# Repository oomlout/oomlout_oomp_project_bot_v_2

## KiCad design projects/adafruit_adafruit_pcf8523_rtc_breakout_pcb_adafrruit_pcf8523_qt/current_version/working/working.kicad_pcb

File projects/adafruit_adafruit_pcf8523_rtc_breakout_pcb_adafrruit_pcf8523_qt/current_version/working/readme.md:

# adafruit_pcf8523_rtc_breakout_pcb
 
## summary 
* id: adafruit_adafruit_pcf8523_rtc_breakout_pcb_adafrruit_pcf8523_qt
* user: adafruit
* name: adafruit_pcf8523_rtc_breakout_pcb
* board: adafrruit_pcf8523_qt
* repo: https://github.com/adafruit/Adafruit-PCF8523-RTC-Breakout-PCB

* src_file_repo_sch: 
* src_file_repo_sch_link: https://github.com/adafruit/Adafruit-PCF8523-RTC-Breakout-PCB/tree/master/
* full details link: https://github.com/oomlout/oomlout_oomp_project_bot_v_2/tree/main/projects/adafruit_adafruit_pcf8523_rtc_breakout_pcb_adafrruit_pcf8523_qt/current_version/working  

## schematic  
  
[schematic (pdf)](working_schematic.pdf) 

## pcb  

[board (pdf)](working.pdf)  

## working_bom
| Id | Designator | Footprint | Quantity | Designation | Supplier and ref |  | None | 
| --- | --- | --- | --- | --- | --- | --- | --- | 
| 1 | CONN3,CONN4 | JST_SH4 | 2 | STEMMA_I2C_QT |  |  | [''] | 
| 2 | D1 | CHIPLED_0603_NOOUTLINE | 1 | GREEN |  |  | [''] | 
| 3 | U$22 | ADAFRUIT_3.5MM | 1 |  |  |  | [''] | 
| 4 | R3 | 0603-NO | 1 | 1K |  |  | [''] | 
| 5 | IC1 | SOIC8_150MIL | 1 | RTC_PCF8523T |  |  | [''] | 
| 6 | R1 | RESPACK_4X0603 | 1 | 10K |  |  | [''] | 
| 7 | U$19,U$21,U$17,U$9 | MOUNTINGHOLE_3.0_PLATEDTHIN | 4 | MOUNTINGHOLE3.0THIN |  |  | [''] | 
| 8 | C4,C3,C1 | 0805-NO | 3 | 10uF |  |  | [''] | 
| 9 | SJ1 | SOLDERJUMPER_CLOSEDWIRE | 1 |  |  |  | [''] | 
| 10 | JP2 | 1X05_ROUND_70 | 1 |  |  |  | [''] | 
| 11 | FID3,FID4,FID1,FID2 | FIDUCIAL_1MM | 4 | FIDUCIAL_1MM |  |  | [''] | 
| 12 | C5 | 0603-NO | 1 | 0.1uF |  |  | [''] | 
| 13 | Q1 | XTAL3215 | 1 | 32.768 |  |  | [''] | 
| 14 | U$25 | PCBFEAT-REV-040 | 1 |  |  |  | [''] | 
| 15 | U$31 | STEMMAQT | 1 |  |  |  | [''] | 
| 16 | B1 | CR1220 | 1 | CR1220 |  |  | [''] | 

## bom_schematic
| Ref | Qnty | Value | Cmp name | Footprint | Description | Vendor | DNP | 
| --- | --- | --- | --- | --- | --- | --- | --- | 
| B1 | 1 | CR1220 | BATTERYCR1220_SMT | working:CR1220 |  |  |  | 
| C1, C3, C4 | 3 | 10uF | CAP_CERAMIC0805-NOOUTLINE | working:0805-NO |  |  |  | 
| C5 | 1 | 0.1uF | CAP_CERAMIC0603_NO | working:0603-NO |  |  |  | 
| CONN3, CONN4 | 2 | STEMMA_I2C_QT | STEMMA_I2C_QT | working:JST_SH4 |  |  |  | 
| D1 | 1 | GREEN | LED0603_NOOUTLINE | working:CHIPLED_0603_NOOUTLINE |  |  |  | 
| FID1, FID2, FID3, FID4 | 4 | FIDUCIAL_1MM | FIDUCIAL_1MM | working:FIDUCIAL_1MM |  |  |  | 
| IC1 | 1 | RTC_PCF8523T | RTC_PCF8523T | working:SOIC8_150MIL |  |  |  | 
| JP2 | 1 | HEADER-1X570MIL | HEADER-1X570MIL | working:1X05_ROUND_70 |  |  |  | 
| Q1 | 1 | 32.768 | CRYSTAL_3215 | working:XTAL3215 |  |  |  | 
| R1 | 1 | 10K | RESISTOR_4PACK | working:RESPACK_4X0603 |  |  |  | 
| R3 | 1 | 1K | RESISTOR_0603_NOOUT | working:0603-NO |  |  |  | 
| SJ1 | 1 | SOLDERJUMPER_CLOSED | SOLDERJUMPER_CLOSED | working:SOLDERJUMPER_CLOSEDWIRE |  |  |  | 
| U$9, U$17, U$19, U$21 | 4 | MOUNTINGHOLE3.0THIN | MOUNTINGHOLE3.0THIN | working:MOUNTINGHOLE_3.0_PLATEDTHIN |  |  |  | 

## mounting_holes
| x | y | package | value | ref | size | 
| --- | --- | --- | --- | --- | --- | 
| 0.0 | 12.7 | MOUNTINGHOLE_3.0_PLATEDTHIN | MOUNTINGHOLE3.0THIN | U$9 | m3 | 
| 20.32 | 12.7 | MOUNTINGHOLE_3.0_PLATEDTHIN | MOUNTINGHOLE3.0THIN | U$17 | m3 | 
| 0.0 | 0.0 | MOUNTINGHOLE_3.0_PLATEDTHIN | MOUNTINGHOLE3.0THIN | U$19 | m3 | 
| 20.32 | 0.0 | MOUNTINGHOLE_3.0_PLATEDTHIN | MOUNTINGHOLE3.0THIN | U$21 | m3 |

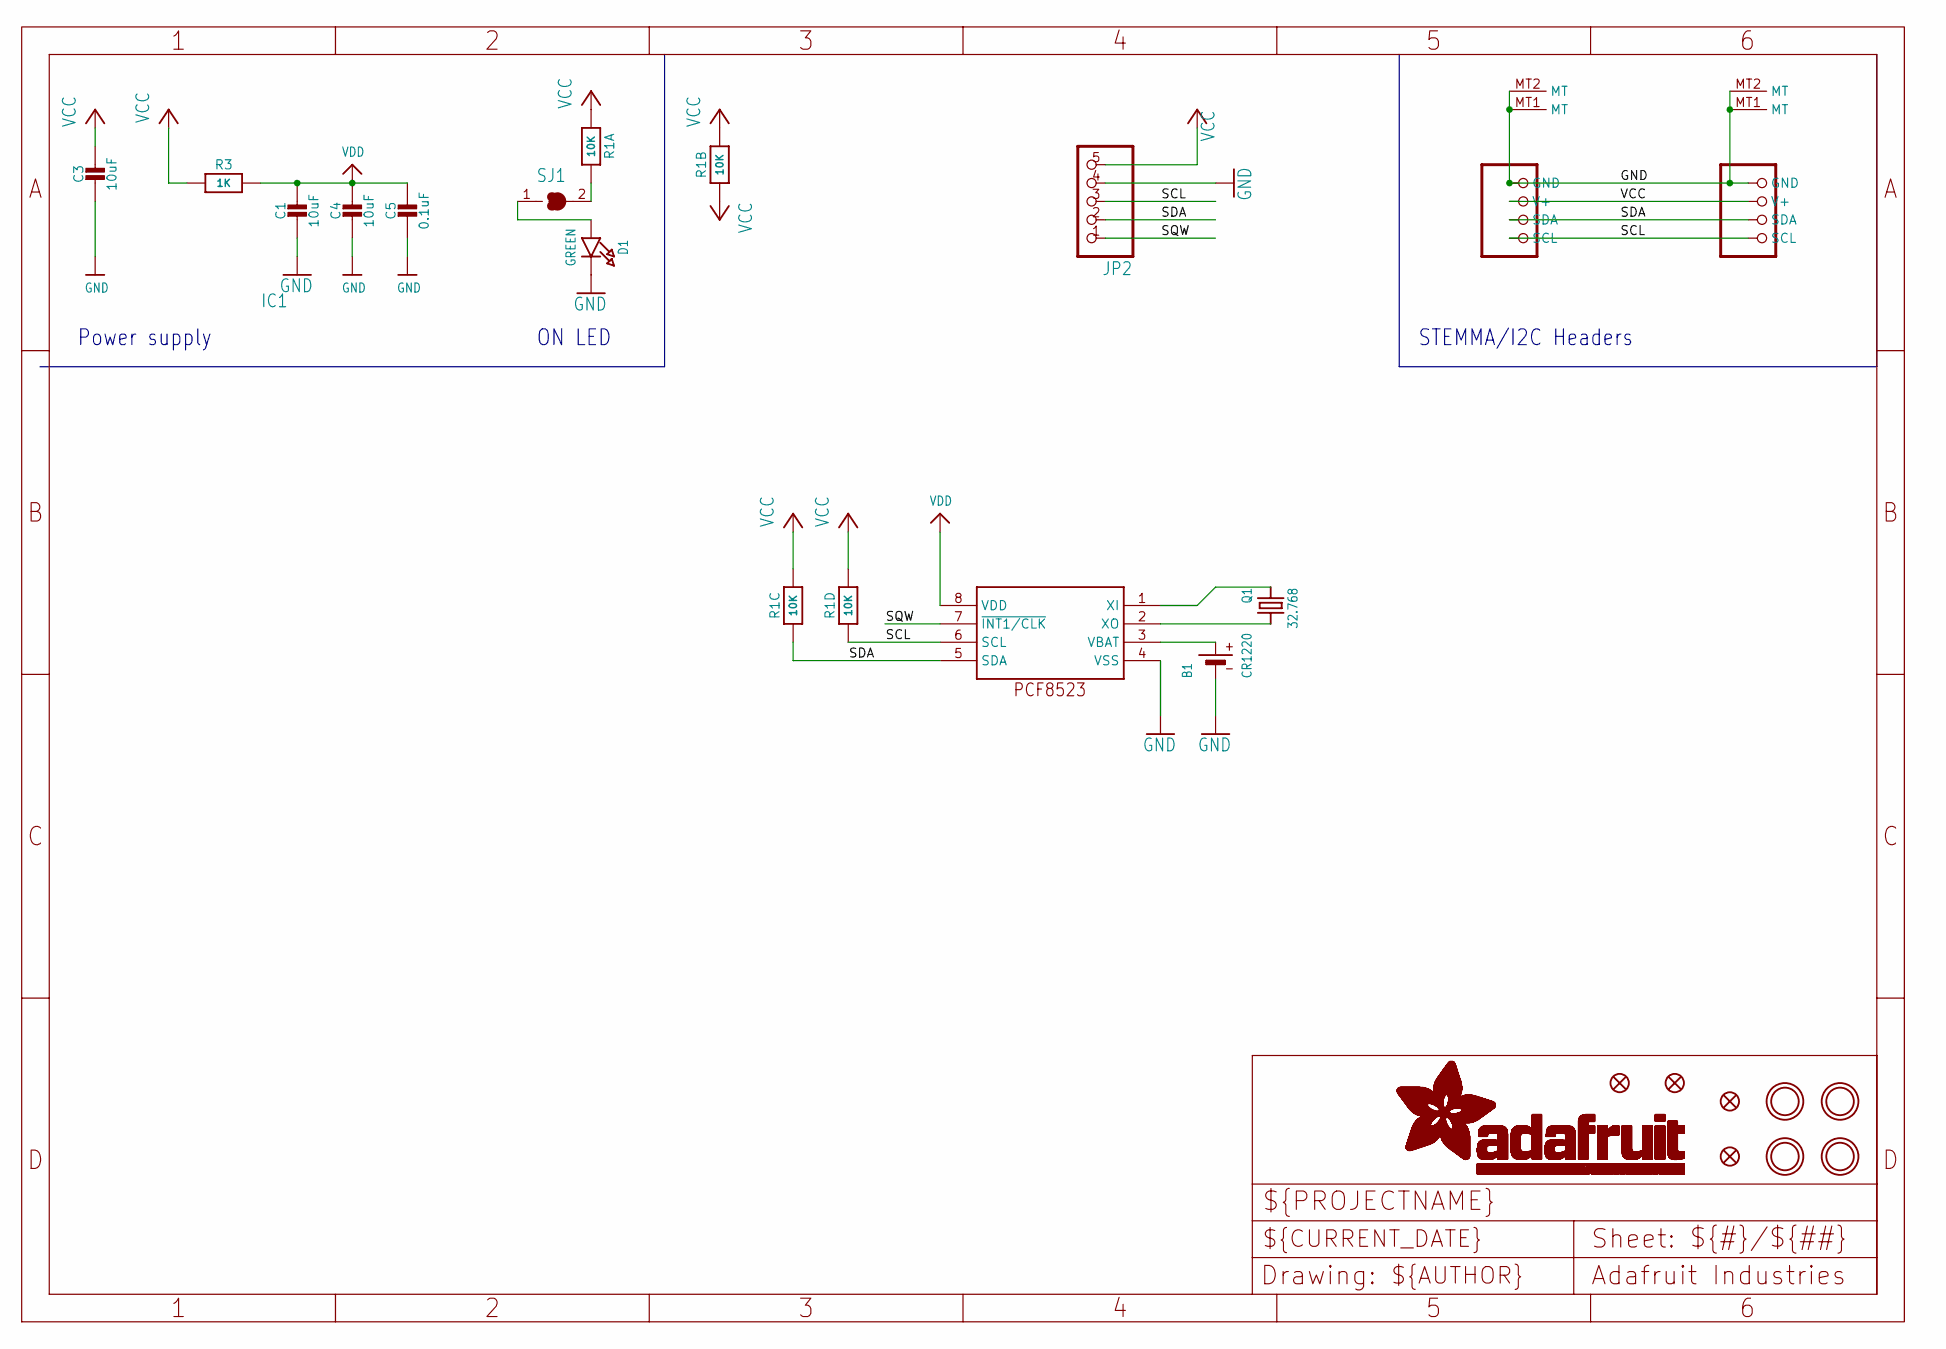
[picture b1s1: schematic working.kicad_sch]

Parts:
B1: CR1220
C1, C3, C4: 10uF; 0805-NO
C5: 0.1uF; 0603-NO
CONN3, CONN4: STEMMA_I2C_QT; JST_SH4
D1: GREEN; CHIPLED_0603_NOOUTLINE
FID1, FID2, FID3, FID4: FIDUCIAL_1MM
IC1: RTC_PCF8523T; SOIC8_150MIL
JP2: HEADER-1X570MIL; 1X05_ROUND_70
Q1: 32.768; XTAL3215
R1: 10K; RESPACK_4X0603
R3: 1K; 0603-NO
SJ1: SOLDERJUMPER_CLOSED; SOLDERJUMPER_CLOSEDWIRE
U$9, U$17, U$19, U$21: MOUNTINGHOLE3.0THIN; MOUNTINGHOLE_3.0_PLATEDTHIN

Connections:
GND: B1.-, C1.2, C3.2, C4.2, C5.2, CONN3.1 (GND), CONN3.MT1 (MT), CONN3.MT2 (MT), CONN4.1 (GND), CONN4.MT1 (MT), CONN4.MT2 (MT), D1.C, IC1.4 (VSS), JP2.4
unnamed: R1.8 (2), SJ1.2
unnamed: D1.A, SJ1.1
unnamed: IC1.1 (XI), Q1.P$1 (1)
unnamed: IC1.2 (XO), Q1.P$2 (2)
SCL: CONN3.4 (SCL), CONN4.4 (SCL), IC1.6 (SCL), JP2.3, R1.4 (1)
SDA: CONN3.3 (SDA), CONN4.3 (SDA), IC1.5 (SDA), JP2.2, R1.3 (1)
SQW: IC1.7 (~INT1/CLK), JP2.1
VBAT: B1.+$1 (+), B1.+$2 (+), IC1.3 (VBAT)
VCC: C3.1, CONN3.2 (V+), CONN4.2 (V+), JP2.5, R1.1, R1.2 (1), R1.5 (2), R1.6 (2), R1.7 (2), R3.1
VDD: C1.1, C4.1, C5.1, IC1.8 (VDD), R3.2

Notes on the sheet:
STEMMA/I2C Headers
Power supply
ON LED

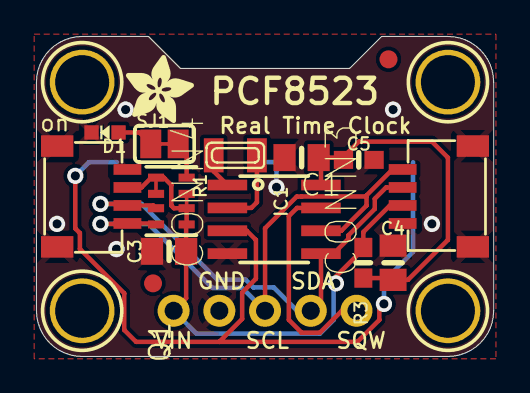
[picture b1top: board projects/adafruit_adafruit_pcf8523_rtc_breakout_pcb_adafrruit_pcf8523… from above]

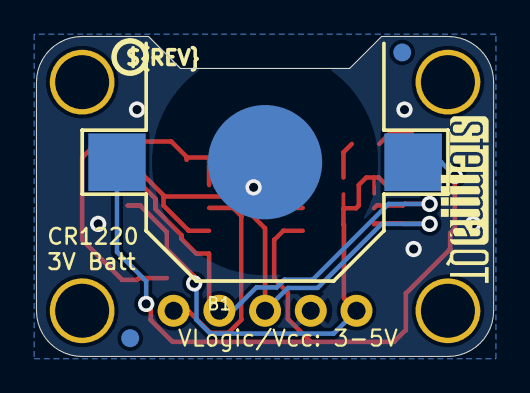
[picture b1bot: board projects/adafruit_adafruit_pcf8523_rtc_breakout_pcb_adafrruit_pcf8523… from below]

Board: 16 copper layers, 25.4 x 17.8 mm, 25 parts (5 on the bottom side), 11 nets.

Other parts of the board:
U$22: ADAFRUIT_3.5MM
U$25: PCBFEAT-REV-040
U$31: STEMMAQT

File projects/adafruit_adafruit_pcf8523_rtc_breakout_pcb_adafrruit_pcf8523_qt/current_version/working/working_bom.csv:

"Id";"Designator";"Footprint";"Quantity";"Designation";"Supplier and ref";
1;"CONN3,CONN4";"JST_SH4";2;"STEMMA_I2C_QT";;;
2;"D1";"CHIPLED_0603_NOOUTLINE";1;"GREEN";;;
3;"U$22";"ADAFRUIT_3.5MM";1;"";;;
4;"R3";"0603-NO";1;"1K";;;
5;"IC1";"SOIC8_150MIL";1;"RTC_PCF8523T";;;
6;"R1";"RESPACK_4X0603";1;"10K";;;
7;"U$19,U$21,U$17,U$9";"MOUNTINGHOLE_3.0_PLATEDTHIN";4;"MOUNTINGHOLE3.0THIN";;;
8;"C4,C3,C1";"0805-NO";3;"10uF";;;
9;"SJ1";"SOLDERJUMPER_CLOSEDWIRE";1;"";;;
10;"JP2";"1X05_ROUND_70";1;"";;;
11;"FID3,FID4,FID1,FID2";"FIDUCIAL_1MM";4;"FIDUCIAL_1MM";;;
12;"C5";"0603-NO";1;"0.1uF";;;
13;"Q1";"XTAL3215";1;"32.768";;;
14;"U$25";"PCBFEAT-REV-040";1;"";;;
15;"U$31";"STEMMAQT";1;"";;;
16;"B1";"CR1220";1;"CR1220";;;

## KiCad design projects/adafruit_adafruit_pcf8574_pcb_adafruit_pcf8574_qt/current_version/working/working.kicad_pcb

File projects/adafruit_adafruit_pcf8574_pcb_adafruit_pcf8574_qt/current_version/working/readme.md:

# adafruit_pcf8574_pcb
 
## summary 
* id: adafruit_adafruit_pcf8574_pcb_adafruit_pcf8574_qt
* user: adafruit
* name: adafruit_pcf8574_pcb
* board: adafruit_pcf8574_qt
* repo: https://github.com/adafruit/Adafruit-PCF8574-PCB

* src_file_repo_sch: 
* src_file_repo_sch_link: https://github.com/adafruit/Adafruit-PCF8574-PCB/tree/main/
* full details link: https://github.com/oomlout/oomlout_oomp_project_bot_v_2/tree/main/projects/adafruit_adafruit_pcf8574_pcb_adafruit_pcf8574_qt/current_version/working  

## schematic  
  
[schematic (pdf)](working_schematic.pdf) 

## pcb  

[board (pdf)](working.pdf)  

## working_bom
| Id | Designator | Footprint | Quantity | Designation | Supplier and ref |  | None | 
| --- | --- | --- | --- | --- | --- | --- | --- | 
| 1 | U$19,U$21 | MOUNTINGHOLE_2.5_PLATED | 2 | MOUNTINGHOLE2.5 |  |  | [''] | 
| 2 | IC1 | VQFN20_3.5X4.5 | 1 | PCF8574RGY |  |  | [''] | 
| 3 | FID4,FID3 | FIDUCIAL_1MM | 2 | FIDUCIAL_1MM |  |  | [''] | 
| 4 | R3,R1 | RESPACK_4X0603 | 2 | 10K |  |  | [''] | 
| 5 | CONN4,CONN3 | JST_SH4 | 2 | STEMMA_I2C_QT |  |  | [''] | 
| 6 | D1 | CHIPLED_0603_NOOUTLINE | 1 | GREEN |  |  | [''] | 
| 7 | U$11 | SYMBOL_PLUS | 1 |  |  |  | [''] | 
| 8 | C1 | 0603-NO | 1 | 0.1uF |  |  | [''] | 
| 9 | U$9 | SYMBOL_MINUS | 1 |  |  |  | [''] | 
| 10 | JP1 | 1X06_ROUND_70 | 1 |  |  |  | [''] | 
| 11 | C3 | 0805-NO | 1 | 10uF |  |  | [''] | 
| 12 | JP3 | 1X10_ROUND70 | 1 |  |  |  | [''] | 
| 13 | U$8 | ADAFRUIT_2.5MM | 1 |  |  |  | [''] | 
| 14 | SJ4 | SOLDERJUMPER_CLOSEDWIRE | 1 |  |  |  | [''] | 
| 15 | SJ1,SJ2,SJ3 | SOLDERJUMPER_ARROW_NOPASTE | 3 |  |  |  | [''] | 
| 16 | U$25 | PCBFEAT-REV-040 | 1 |  |  |  | [''] | 
| 17 | U$30,U$31 | STEMMAQT | 2 |  |  |  | [''] | 

## bom_schematic
| Ref | Qnty | Value | Cmp name | Footprint | Description | Vendor | DNP | 
| --- | --- | --- | --- | --- | --- | --- | --- | 
| C1 | 1 | 0.1uF | CAP_CERAMIC0603_NO | working:0603-NO |  |  |  | 
| C3 | 1 | 10uF | CAP_CERAMIC0805-NOOUTLINE | working:0805-NO |  |  |  | 
| CONN3, CONN4 | 2 | STEMMA_I2C_QT | STEMMA_I2C_QT | working:JST_SH4 |  |  |  | 
| D1 | 1 | GREEN | LED0603_NOOUTLINE | working:CHIPLED_0603_NOOUTLINE |  |  |  | 
| FID3, FID4 | 2 | FIDUCIAL_1MM | FIDUCIAL_1MM | working:FIDUCIAL_1MM |  |  |  | 
| IC1 | 1 | PCF8574RGY | PCF8574RGY | working:VQFN20_3.5X4.5 |  |  |  | 
| JP1 | 1 | HEADER-1X670MIL | HEADER-1X670MIL | working:1X06_ROUND_70 |  |  |  | 
| JP3 | 1 | HEADER-1X1070MIL | HEADER-1X1070MIL | working:1X10_ROUND70 |  |  |  | 
| R1, R3 | 2 | 10K | RESISTOR_4PACK | working:RESPACK_4X0603 |  |  |  | 
| SJ1, SJ2, SJ3 | 3 | SOLDERJUMPER | SOLDERJUMPER | working:SOLDERJUMPER_ARROW_NOPASTE |  |  |  | 
| SJ4 | 1 | SOLDERJUMPERCLOSED | SOLDERJUMPERCLOSED | working:SOLDERJUMPER_CLOSEDWIRE |  |  |  | 
| U$19, U$21 | 2 | MOUNTINGHOLE2.5 | MOUNTINGHOLE2.5 | working:MOUNTINGHOLE_2.5_PLATED |  |  |  | 

## mounting_holes
| x | y | package | value | ref | size | 
| --- | --- | --- | --- | --- | --- | 
| 0.0 | 0.0 | MOUNTINGHOLE_2.5_PLATED | MOUNTINGHOLE2.5 | U$19 | m3 | 
| 20.32 | 0.0 | MOUNTINGHOLE_2.5_PLATED | MOUNTINGHOLE2.5 | U$21 | m3 |

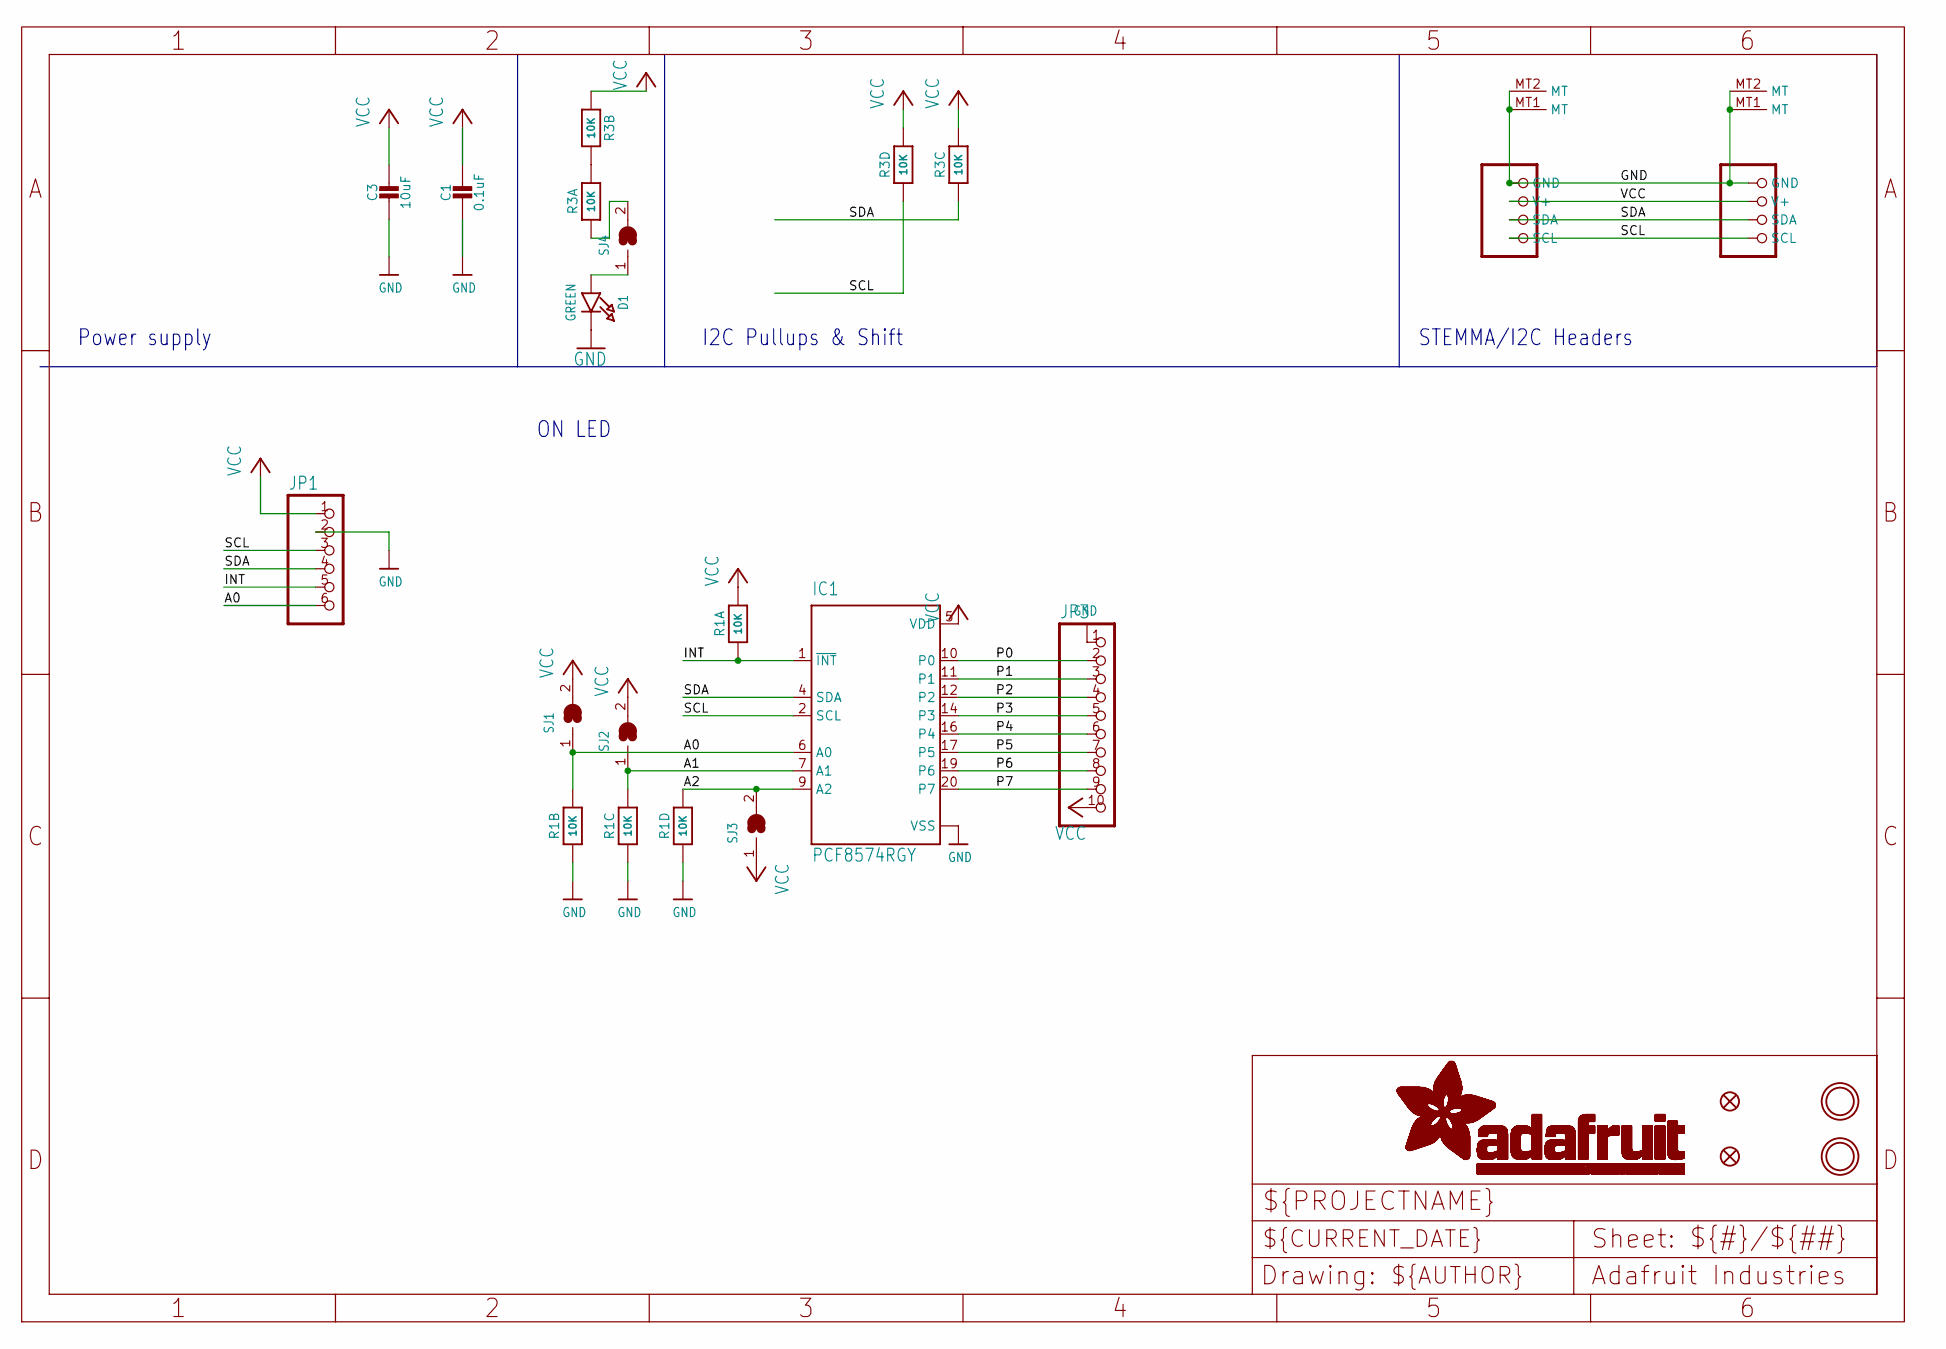
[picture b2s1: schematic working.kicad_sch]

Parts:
C1: 0.1uF; 0603-NO
C3: 10uF; 0805-NO
CONN3, CONN4: STEMMA_I2C_QT; JST_SH4
D1: GREEN; CHIPLED_0603_NOOUTLINE
FID3, FID4: FIDUCIAL_1MM
IC1: PCF8574RGY; VQFN20_3.5X4.5
JP1: HEADER-1X670MIL; 1X06_ROUND_70
JP3: HEADER-1X1070MIL; 1X10_ROUND70
R1, R3: 10K; RESPACK_4X0603
SJ1, SJ2, SJ3: SOLDERJUMPER; SOLDERJUMPER_ARROW_NOPASTE
SJ4: SOLDERJUMPERCLOSED; SOLDERJUMPER_CLOSEDWIRE
U$19, U$21: MOUNTINGHOLE2.5; MOUNTINGHOLE_2.5_PLATED

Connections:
A0: IC1.6 (A0), JP1.6, R1.7 (2), SJ1.1
A1: IC1.7 (A1), R1.6 (2), SJ2.1
A2: IC1.9 (A2), R1.5 (2), SJ3.2
GND: C1.2, C3.2, CONN3.1 (GND), CONN3.MT1 (MT), CONN3.MT2 (MT), CONN4.1 (GND), CONN4.MT1 (MT), CONN4.MT2 (MT), D1.C, IC1.15 (VSS), IC1.21 (VSS), JP1.2, JP3.1, R1.2 (1), R1.3 (1), R1.4 (1)
INT: IC1.1 (~INT), JP1.5, R1.1
unnamed: R3.1, SJ4.2
unnamed: R3.7 (2), R3.8 (2)
unnamed: D1.A, SJ4.1
P0: IC1.10 (P0), JP3.2
P1: IC1.11 (P1), JP3.3
P2: IC1.12 (P2), JP3.4
P3: IC1.14 (P3), JP3.5
P4: IC1.16 (P4), JP3.6
P5: IC1.17 (P5), JP3.7
P6: IC1.19 (P6), JP3.8
P7: IC1.20 (P7), JP3.9
SCL: CONN3.4 (SCL), CONN4.4 (SCL), IC1.2 (SCL), JP1.3, R3.4 (1)
SDA: CONN3.3 (SDA), CONN4.3 (SDA), IC1.4 (SDA), JP1.4, R3.3 (1)
VCC: C1.1, C3.1, CONN3.2 (V+), CONN4.2 (V+), IC1.5 (VDD), JP1.1, JP3.10, R1.8 (2), R3.2 (1), R3.5 (2), R3.6 (2), SJ1.2, SJ2.2, SJ3.1

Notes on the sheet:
STEMMA/I2C Headers
Power supply
I2C Pullups & Shift
ON LED

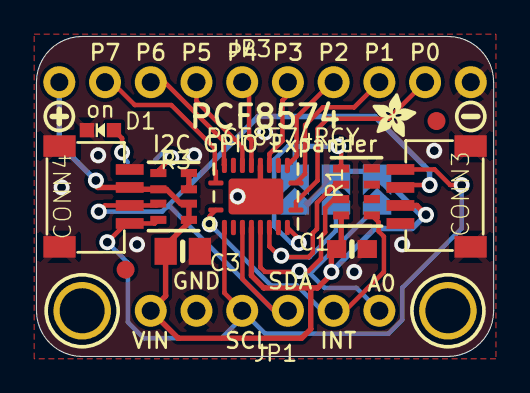
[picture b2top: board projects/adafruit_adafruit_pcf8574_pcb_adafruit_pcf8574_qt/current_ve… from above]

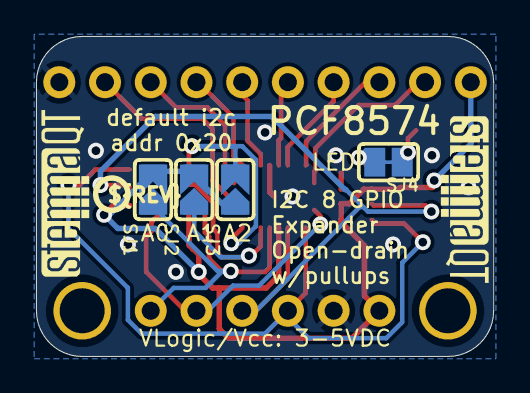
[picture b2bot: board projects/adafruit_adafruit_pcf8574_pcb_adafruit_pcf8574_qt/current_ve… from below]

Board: 2 copper layers, 25.4 x 17.8 mm, 24 parts (7 on the bottom side), 19 nets.

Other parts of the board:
U$8: ADAFRUIT_2.5MM
U$9: SYMBOL_MINUS
U$11: SYMBOL_PLUS
U$25: PCBFEAT-REV-040
U$30, U$31: STEMMAQT

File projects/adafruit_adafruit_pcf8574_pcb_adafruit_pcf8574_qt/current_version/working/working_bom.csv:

"Id";"Designator";"Footprint";"Quantity";"Designation";"Supplier and ref";
1;"U$19,U$21";"MOUNTINGHOLE_2.5_PLATED";2;"MOUNTINGHOLE2.5";;;
2;"IC1";"VQFN20_3.5X4.5";1;"PCF8574RGY";;;
3;"FID4,FID3";"FIDUCIAL_1MM";2;"FIDUCIAL_1MM";;;
4;"R3,R1";"RESPACK_4X0603";2;"10K";;;
5;"CONN4,CONN3";"JST_SH4";2;"STEMMA_I2C_QT";;;
6;"D1";"CHIPLED_0603_NOOUTLINE";1;"GREEN";;;
7;"U$11";"SYMBOL_PLUS";1;"";;;
8;"C1";"0603-NO";1;"0.1uF";;;
9;"U$9";"SYMBOL_MINUS";1;"";;;
10;"JP1";"1X06_ROUND_70";1;"";;;
11;"C3";"0805-NO";1;"10uF";;;
12;"JP3";"1X10_ROUND70";1;"";;;
13;"U$8";"ADAFRUIT_2.5MM";1;"";;;
14;"SJ4";"SOLDERJUMPER_CLOSEDWIRE";1;"";;;
15;"SJ1,SJ2,SJ3";"SOLDERJUMPER_ARROW_NOPASTE";3;"";;;
16;"U$25";"PCBFEAT-REV-040";1;"";;;
17;"U$30,U$31";"STEMMAQT";2;"";;;

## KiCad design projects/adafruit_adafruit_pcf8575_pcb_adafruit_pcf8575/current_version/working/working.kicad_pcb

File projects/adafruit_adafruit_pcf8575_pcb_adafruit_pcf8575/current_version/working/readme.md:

# adafruit_pcf8575_pcb
 
## summary 
* id: adafruit_adafruit_pcf8575_pcb_adafruit_pcf8575
* user: adafruit
* name: adafruit_pcf8575_pcb
* board: adafruit_pcf8575
* repo: https://github.com/adafruit/Adafruit-PCF8575-PCB

* src_file_repo_sch: 
* src_file_repo_sch_link: https://github.com/adafruit/Adafruit-PCF8575-PCB/tree/main/
* full details link: https://github.com/oomlout/oomlout_oomp_project_bot_v_2/tree/main/projects/adafruit_adafruit_pcf8575_pcb_adafruit_pcf8575/current_version/working  

## schematic  
  
[schematic (pdf)](working_schematic.pdf) 

## pcb  

[board (pdf)](working.pdf)  

## working_bom
| Id | Designator | Footprint | Quantity | Designation | Supplier and ref |  | None | 
| --- | --- | --- | --- | --- | --- | --- | --- | 
| 1 | U$17,U$1,U$21,U$19 | MOUNTINGHOLE_2.5_PLATED | 4 | MOUNTINGHOLE2.5 |  |  | [''] | 
| 2 | IC2 | QFN24_4MM_SMSC | 1 | PCF8575 |  |  | [''] | 
| 3 | U$22 | ADAFRUIT_3.5MM | 1 |  |  |  | [''] | 
| 4 | CONN3,CONN4 | JST_SH4 | 2 | STEMMA_I2C_QT |  |  | [''] | 
| 5 | JP6,JP2,JP7,JP8 | 1X08_ROUND_70 | 4 |  |  |  | [''] | 
| 6 | D1 | CHIPLED_0603_NOOUTLINE | 1 | GREEN |  |  | [''] | 
| 7 | FID3,FID4 | FIDUCIAL_1MM | 2 | FIDUCIAL_1MM |  |  | [''] | 
| 8 | R1,R3 | RESPACK_4X0603 | 2 | 10K Pack |  |  | [''] | 
| 9 | U$3 | SYMBOL_MINUS | 1 |  |  |  | [''] | 
| 10 | C1 | 0603-NO | 1 | 0.1uF |  |  | [''] | 
| 11 | C3,C2 | 0805-NO | 2 | 10uF |  |  | [''] | 
| 12 | JP4,JP3 | 1X04_ROUND | 2 |  |  |  | [''] | 
| 13 | U$2 | SYMBOL_PLUS | 1 |  |  |  | [''] | 
| 14 | ADDR2,ADDR1,ADDR0 | SOLDERJUMPER_ARROW_NOPASTE | 3 |  |  |  | [''] | 
| 15 | U$30,U$31 | STEMMAQT | 2 |  |  |  | [''] | 
| 16 | SJ1 | SOLDERJUMPER_CLOSEDWIRE | 1 |  |  |  | [''] | 
| 17 | U$25 | PCBFEAT-REV-040 | 1 |  |  |  | [''] | 

## bom_schematic
| Ref | Qnty | Value | Cmp name | Footprint | Description | Vendor | DNP | 
| --- | --- | --- | --- | --- | --- | --- | --- | 
| ADDR0, ADDR1, ADDR2 | 3 | SOLDERJUMPER | SOLDERJUMPER | working:SOLDERJUMPER_ARROW_NOPASTE |  |  |  | 
| C1 | 1 | 0.1uF | CAP_CERAMIC0603_NO | working:0603-NO |  |  |  | 
| C2, C3 | 2 | 10uF | CAP_CERAMIC0805-NOOUTLINE | working:0805-NO |  |  |  | 
| CONN3, CONN4 | 2 | STEMMA_I2C_QT | STEMMA_I2C_QT | working:JST_SH4 |  |  |  | 
| D1 | 1 | GREEN | LED0603_NOOUTLINE | working:CHIPLED_0603_NOOUTLINE |  |  |  | 
| FID3, FID4 | 2 | FIDUCIAL_1MM | FIDUCIAL_1MM | working:FIDUCIAL_1MM |  |  |  | 
| IC2 | 1 | PCF8575 | PCF8575 | working:QFN24_4MM_SMSC |  |  |  | 
| JP2, JP6, JP7, JP8 | 4 | HEADER-1X870MIL | HEADER-1X870MIL | working:1X08_ROUND_70 |  |  |  | 
| JP3, JP4 | 2 | HEADER-1X4ROUND | HEADER-1X4ROUND | working:1X04_ROUND |  |  |  | 
| R1, R3 | 2 | 10K Pack | RESISTOR_4PACK | working:RESPACK_4X0603 |  |  |  | 
| SJ1 | 1 | SOLDERJUMPERCLOSED | SOLDERJUMPERCLOSED | working:SOLDERJUMPER_CLOSEDWIRE |  |  |  | 
| U$1, U$17, U$19, U$21 | 4 | MOUNTINGHOLE2.5 | MOUNTINGHOLE2.5 | working:MOUNTINGHOLE_2.5_PLATED |  |  |  | 

## mounting_holes
| x | y | package | value | ref | size | 
| --- | --- | --- | --- | --- | --- | 
| 0.0 | 12.7 | MOUNTINGHOLE_2.5_PLATED | MOUNTINGHOLE2.5 | U$1 | m3 | 
| 35.56 | 12.7 | MOUNTINGHOLE_2.5_PLATED | MOUNTINGHOLE2.5 | U$17 | m3 | 
| 0.0 | 0.0 | MOUNTINGHOLE_2.5_PLATED | MOUNTINGHOLE2.5 | U$19 | m3 | 
| 35.56 | 0.0 | MOUNTINGHOLE_2.5_PLATED | MOUNTINGHOLE2.5 | U$21 | m3 |

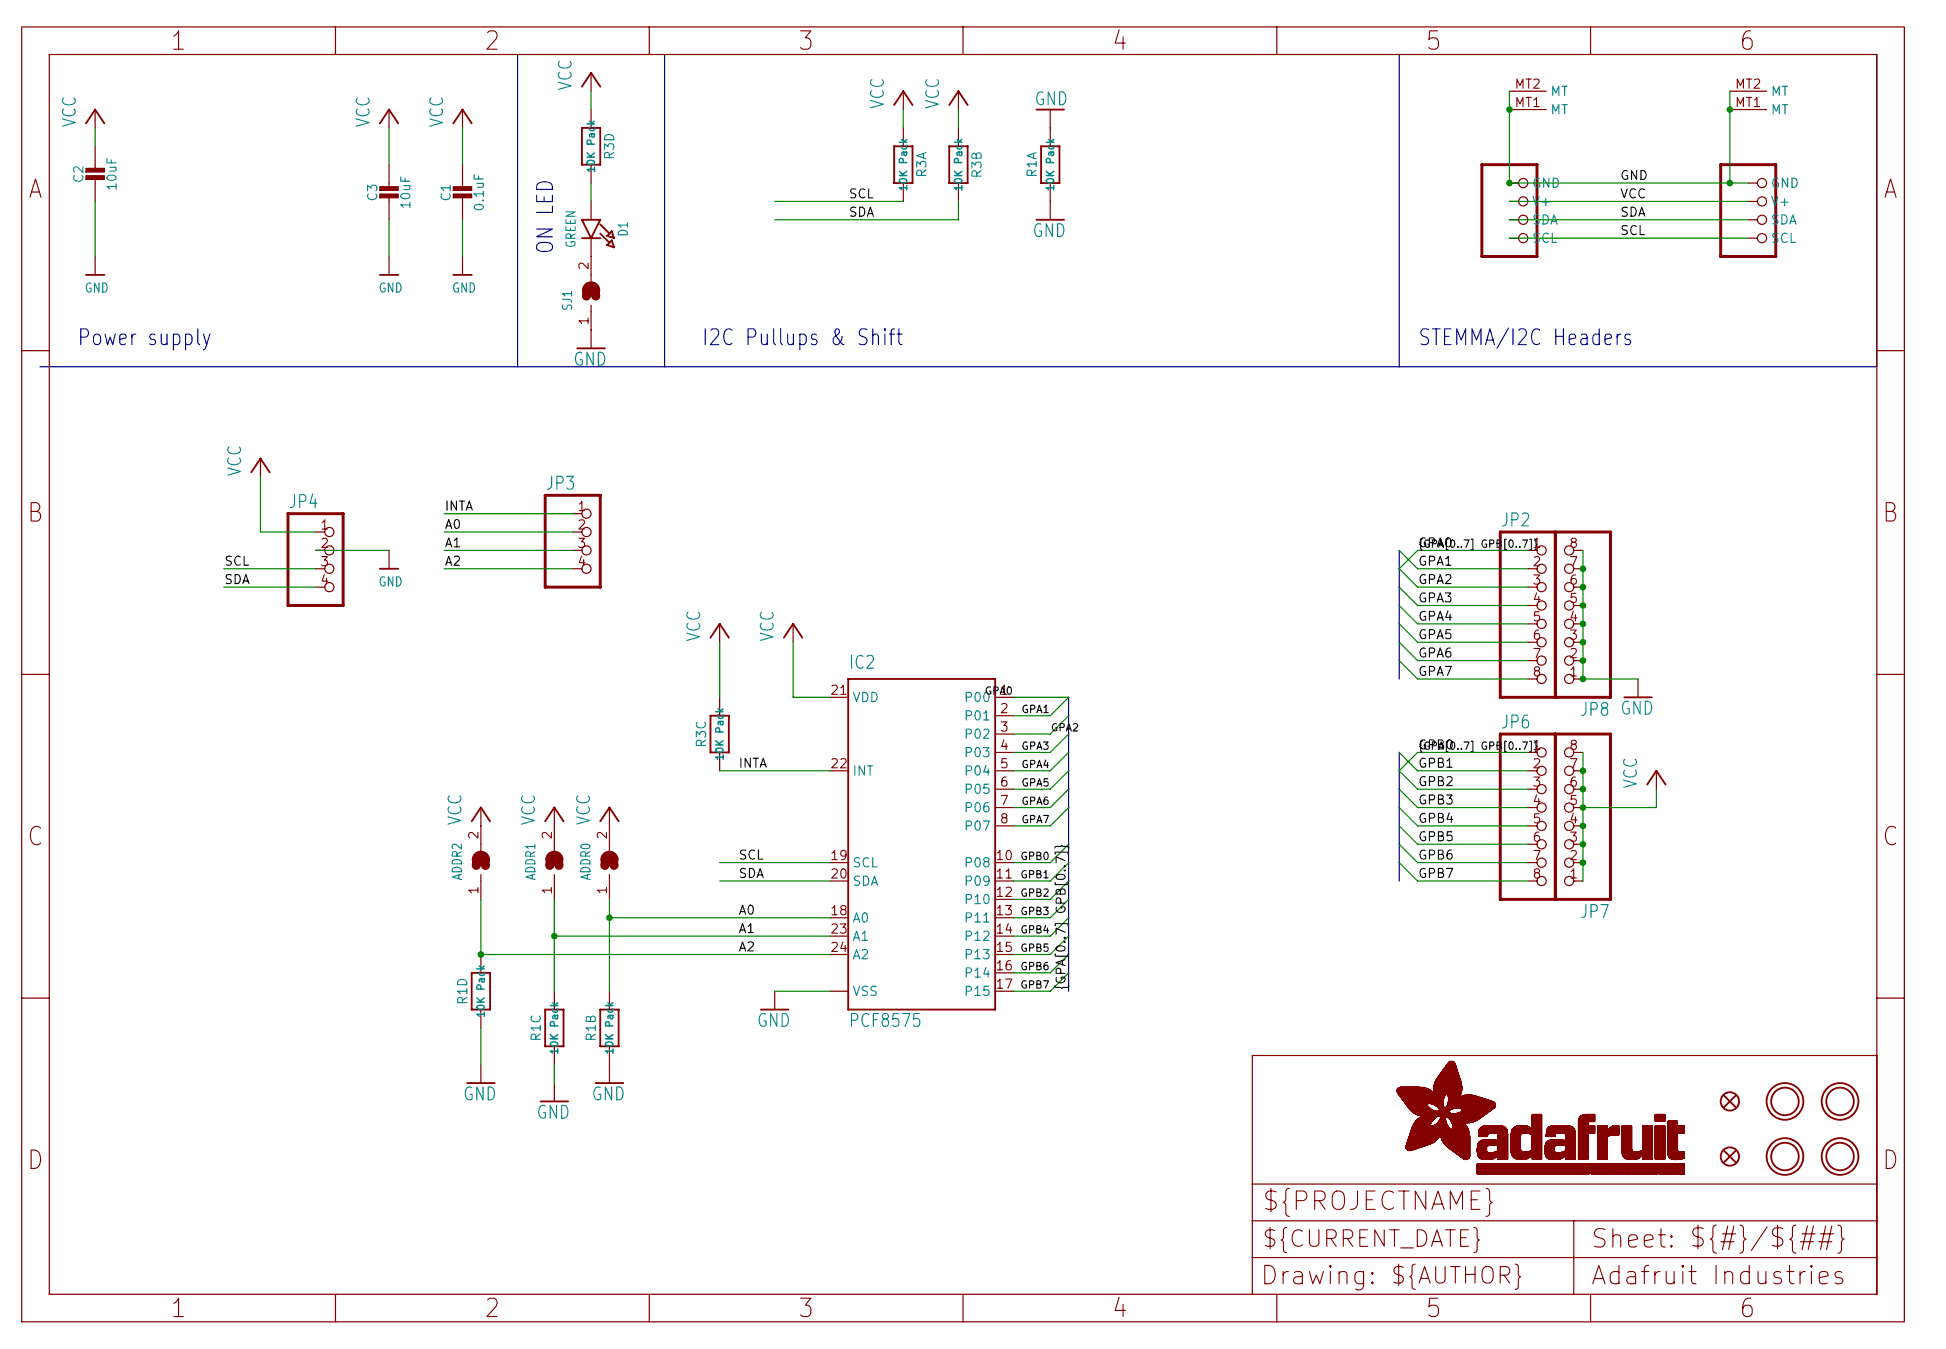
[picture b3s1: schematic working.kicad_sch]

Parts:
ADDR0, ADDR1, ADDR2: SOLDERJUMPER; SOLDERJUMPER_ARROW_NOPASTE
C1: 0.1uF; 0603-NO
C2, C3: 10uF; 0805-NO
CONN3, CONN4: STEMMA_I2C_QT; JST_SH4
D1: GREEN; CHIPLED_0603_NOOUTLINE
FID3, FID4: FIDUCIAL_1MM
IC2: PCF8575; QFN24_4MM_SMSC
JP2, JP6, JP7, JP8: HEADER-1X870MIL; 1X08_ROUND_70
JP3, JP4: HEADER-1X4ROUND; 1X04_ROUND
R1, R3: 10K Pack; RESPACK_4X0603
SJ1: SOLDERJUMPERCLOSED; SOLDERJUMPER_CLOSEDWIRE
U$1, U$17, U$19, U$21: MOUNTINGHOLE2.5; MOUNTINGHOLE_2.5_PLATED

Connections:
A0: ADDR0.1, IC2.18 (A0), JP3.2, R1.7 (2)
A1: ADDR1.1, IC2.23 (A1), JP3.3, R1.6 (2)
A2: ADDR2.1, IC2.24 (A2), JP3.4, R1.5 (2)
GND: C1.2, C2.2, C3.2, CONN3.1 (GND), CONN3.MT1 (MT), CONN3.MT2 (MT), CONN4.1 (GND), CONN4.MT1 (MT), CONN4.MT2 (MT), IC2.9 (VSS), IC2.THERM (VSS), JP4.2, JP8.1, JP8.2, JP8.3, JP8.4, JP8.5, JP8.6, JP8.7, JP8.8, R1.1, R1.2 (1), R1.3 (1), R1.4 (1), R1.8 (2), SJ1.1
GPA1: IC2.2 (P01), JP2.2
GPA2: IC2.3 (P02), JP2.3
GPA3: IC2.4 (P03), JP2.4
GPA4: IC2.5 (P04), JP2.5
GPA5: IC2.6 (P05), JP2.6
GPA6: IC2.7 (P06), JP2.7
GPA7: IC2.8 (P07), JP2.8
GPB1: IC2.11 (P09), JP6.2
GPB2: IC2.12 (P10), JP6.3
GPB3: IC2.13 (P11), JP6.4
GPB4: IC2.14 (P12), JP6.5
GPB5: IC2.15 (P13), JP6.6
GPB6: IC2.16 (P14), JP6.7
GPB7: IC2.17 (P15), JP6.8
INTA: IC2.22 (INT), JP3.1, R3.3 (1)
unnamed: D1.A, R3.5 (2)
unnamed: D1.C, SJ1.2
SCL: CONN3.4 (SCL), CONN4.4 (SCL), IC2.19 (SCL), JP4.3, R3.8 (2)
SDA: CONN3.3 (SDA), CONN4.3 (SDA), IC2.20 (SDA), JP4.4, R3.7 (2)
VCC: ADDR0.2, ADDR1.2, ADDR2.2, C1.1, C2.1, C3.1, CONN3.2 (V+), CONN4.2 (V+), IC2.21 (VDD), JP4.1, JP7.1, JP7.2, JP7.3, JP7.4, JP7.5, JP7.6, JP7.7, JP7.8, R3.1, R3.2 (1), R3.4 (1), R3.6 (2)

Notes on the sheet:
I2C Pullups & Shift
ON LED
STEMMA/I2C Headers
Power supply

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
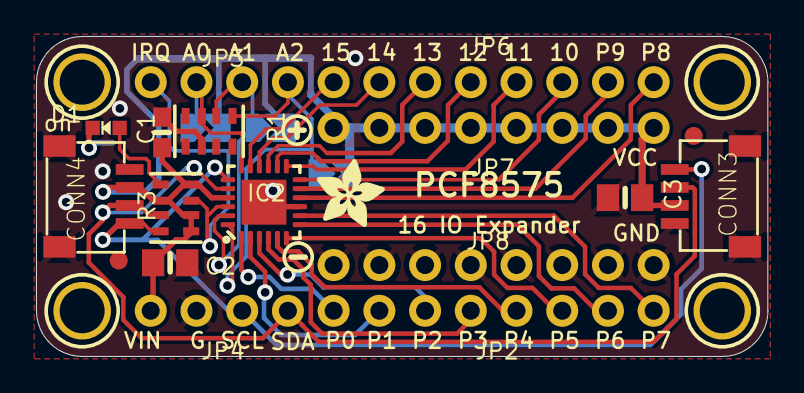
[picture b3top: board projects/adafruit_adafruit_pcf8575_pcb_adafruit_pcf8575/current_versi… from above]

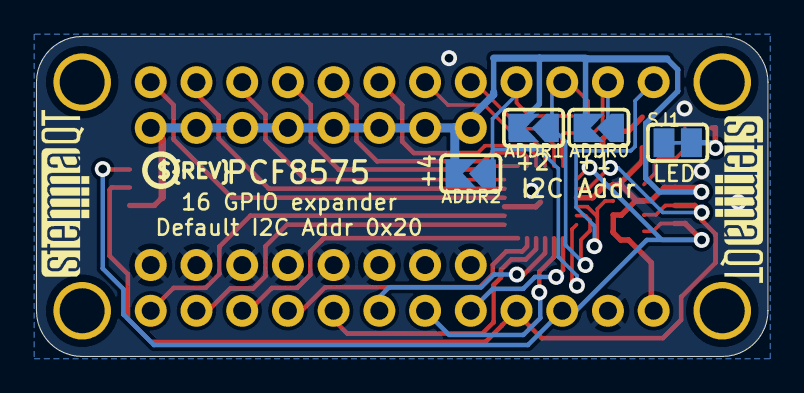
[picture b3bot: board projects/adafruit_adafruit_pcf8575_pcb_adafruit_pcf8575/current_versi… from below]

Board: 2 copper layers, 40.6 x 17.8 mm, 31 parts (7 on the bottom side), 26 nets.

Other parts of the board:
U$2: SYMBOL_PLUS
U$3: SYMBOL_MINUS
U$22: ADAFRUIT_3.5MM
U$25: PCBFEAT-REV-040
U$30, U$31: STEMMAQT

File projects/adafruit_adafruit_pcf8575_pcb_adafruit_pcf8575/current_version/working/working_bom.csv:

"Id";"Designator";"Footprint";"Quantity";"Designation";"Supplier and ref";
1;"U$17,U$1,U$21,U$19";"MOUNTINGHOLE_2.5_PLATED";4;"MOUNTINGHOLE2.5";;;
2;"IC2";"QFN24_4MM_SMSC";1;"PCF8575";;;
3;"U$22";"ADAFRUIT_3.5MM";1;"";;;
4;"CONN3,CONN4";"JST_SH4";2;"STEMMA_I2C_QT";;;
5;"JP6,JP2,JP7,JP8";"1X08_ROUND_70";4;"";;;
6;"D1";"CHIPLED_0603_NOOUTLINE";1;"GREEN";;;
7;"FID3,FID4";"FIDUCIAL_1MM";2;"FIDUCIAL_1MM";;;
8;"R1,R3";"RESPACK_4X0603";2;"10K Pack";;;
9;"U$3";"SYMBOL_MINUS";1;"";;;
10;"C1";"0603-NO";1;"0.1uF";;;
11;"C3,C2";"0805-NO";2;"10uF";;;
12;"JP4,JP3";"1X04_ROUND";2;"";;;
13;"U$2";"SYMBOL_PLUS";1;"";;;
14;"ADDR2,ADDR1,ADDR0";"SOLDERJUMPER_ARROW_NOPASTE";3;"";;;
15;"U$30,U$31";"STEMMAQT";2;"";;;
16;"SJ1";"SOLDERJUMPER_CLOSEDWIRE";1;"";;;
17;"U$25";"PCBFEAT-REV-040";1;"";;;

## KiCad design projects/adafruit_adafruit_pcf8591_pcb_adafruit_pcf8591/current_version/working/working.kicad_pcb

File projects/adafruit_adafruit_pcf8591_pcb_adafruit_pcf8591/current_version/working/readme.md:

# adafruit_pcf8591_pcb
 
## summary 
* id: adafruit_adafruit_pcf8591_pcb_adafruit_pcf8591
* user: adafruit
* name: adafruit_pcf8591_pcb
* board: adafruit_pcf8591
* repo: https://github.com/adafruit/Adafruit-PCF8591-PCB

* src_file_repo_sch: 
* src_file_repo_sch_link: https://github.com/adafruit/Adafruit-PCF8591-PCB/tree/master/
* full details link: https://github.com/oomlout/oomlout_oomp_project_bot_v_2/tree/main/projects/adafruit_adafruit_pcf8591_pcb_adafruit_pcf8591/current_version/working  

## schematic  
  
[schematic (pdf)](working_schematic.pdf) 

## pcb  

[board (pdf)](working.pdf)  

## working_bom
| Id | Designator | Footprint | Quantity | Designation | Supplier and ref |  | None | 
| --- | --- | --- | --- | --- | --- | --- | --- | 
| 1 | U$21,U$19 | MOUNTINGHOLE_2.5_PLATED | 2 | MOUNTINGHOLE2.5 |  |  | [''] | 
| 2 | FID3,FID4 | FIDUCIAL_1MM | 2 | FIDUCIAL_1MM |  |  | [''] | 
| 3 | D1 | CHIPLED_0603_NOOUTLINE | 1 | GREEN |  |  | [''] | 
| 4 | C1 | 0603-NO | 1 | 0.1uF |  |  | [''] | 
| 5 | R3,R1 | RESPACK_4X0603 | 2 | 10K |  |  | [''] | 
| 6 | JP3 | 1X07_ROUND_70 | 1 |  |  |  | [''] | 
| 7 | CONN3,CONN4 | JST_SH4 | 2 | STEMMA_I2C_QT |  |  | [''] | 
| 8 | @HOLE0,@HOLE1 |  | 2 |  |  |  | [''] | 
| 9 | C3 | 0805-NO | 1 | 10uF |  |  | [''] | 
| 10 | R2 | 0603-NO | 1 | 1K |  |  | [''] | 
| 11 | IC1 | SO16W | 1 | PCF8591T |  |  | [''] | 
| 12 | JP2 | 1X05_ROUND_70 | 1 |  |  |  | [''] | 
| 13 | U$22 | ADAFRUIT_3.5MM | 1 |  |  |  | [''] | 
| 14 | U$30,U$31 | STEMMAQT | 2 |  |  |  | [''] | 
| 15 | SJ2,SJ4,SJ1,SJ3 | SOLDERJUMPER_ARROW_NOPASTE | 4 |  |  |  | [''] | 
| 16 | U$25 | PCBFEAT-REV-040 | 1 |  |  |  | [''] | 

## bom_schematic
| Ref | Qnty | Value | Cmp name | Footprint | Description | Vendor | DNP | 
| --- | --- | --- | --- | --- | --- | --- | --- | 
| C1 | 1 | 0.1uF | CAP_CERAMIC0603_NO | working:0603-NO |  |  |  | 
| C3 | 1 | 10uF | CAP_CERAMIC0805-NOOUTLINE | working:0805-NO |  |  |  | 
| CONN3, CONN4 | 2 | STEMMA_I2C_QT | STEMMA_I2C_QT | working:JST_SH4 |  |  |  | 
| D1 | 1 | GREEN | LED0603_NOOUTLINE | working:CHIPLED_0603_NOOUTLINE |  |  |  | 
| FID3, FID4 | 2 | FIDUCIAL_1MM | FIDUCIAL_1MM | working:FIDUCIAL_1MM |  |  |  | 
| IC1 | 1 | PCF8591T | PCF8591T | working:SO16W |  |  |  | 
| JP2 | 1 | HEADER-1X570MIL | HEADER-1X570MIL | working:1X05_ROUND_70 |  |  |  | 
| JP3 | 1 | HEADER-1X770MIL | HEADER-1X770MIL | working:1X07_ROUND_70 |  |  |  | 
| R1, R3 | 2 | 10K | RESISTOR_4PACK | working:RESPACK_4X0603 |  |  |  | 
| R2 | 1 | 1K | RESISTOR_0603_NOOUT | working:0603-NO |  |  |  | 
| SJ1, SJ2, SJ3, SJ4 | 4 | SOLDERJUMPER | SOLDERJUMPER | working:SOLDERJUMPER_ARROW_NOPASTE |  |  |  | 
| U$19, U$21 | 2 | MOUNTINGHOLE2.5 | MOUNTINGHOLE2.5 | working:MOUNTINGHOLE_2.5_PLATED |  |  |  | 

## mounting_holes
| x | y | package | value | ref | size | 
| --- | --- | --- | --- | --- | --- | 
| 0.0 | 0.0 | MOUNTINGHOLE_2.5_PLATED | MOUNTINGHOLE2.5 | U$19 | m3 | 
| 20.32 | 0.0 | MOUNTINGHOLE_2.5_PLATED | MOUNTINGHOLE2.5 | U$21 | m3 |

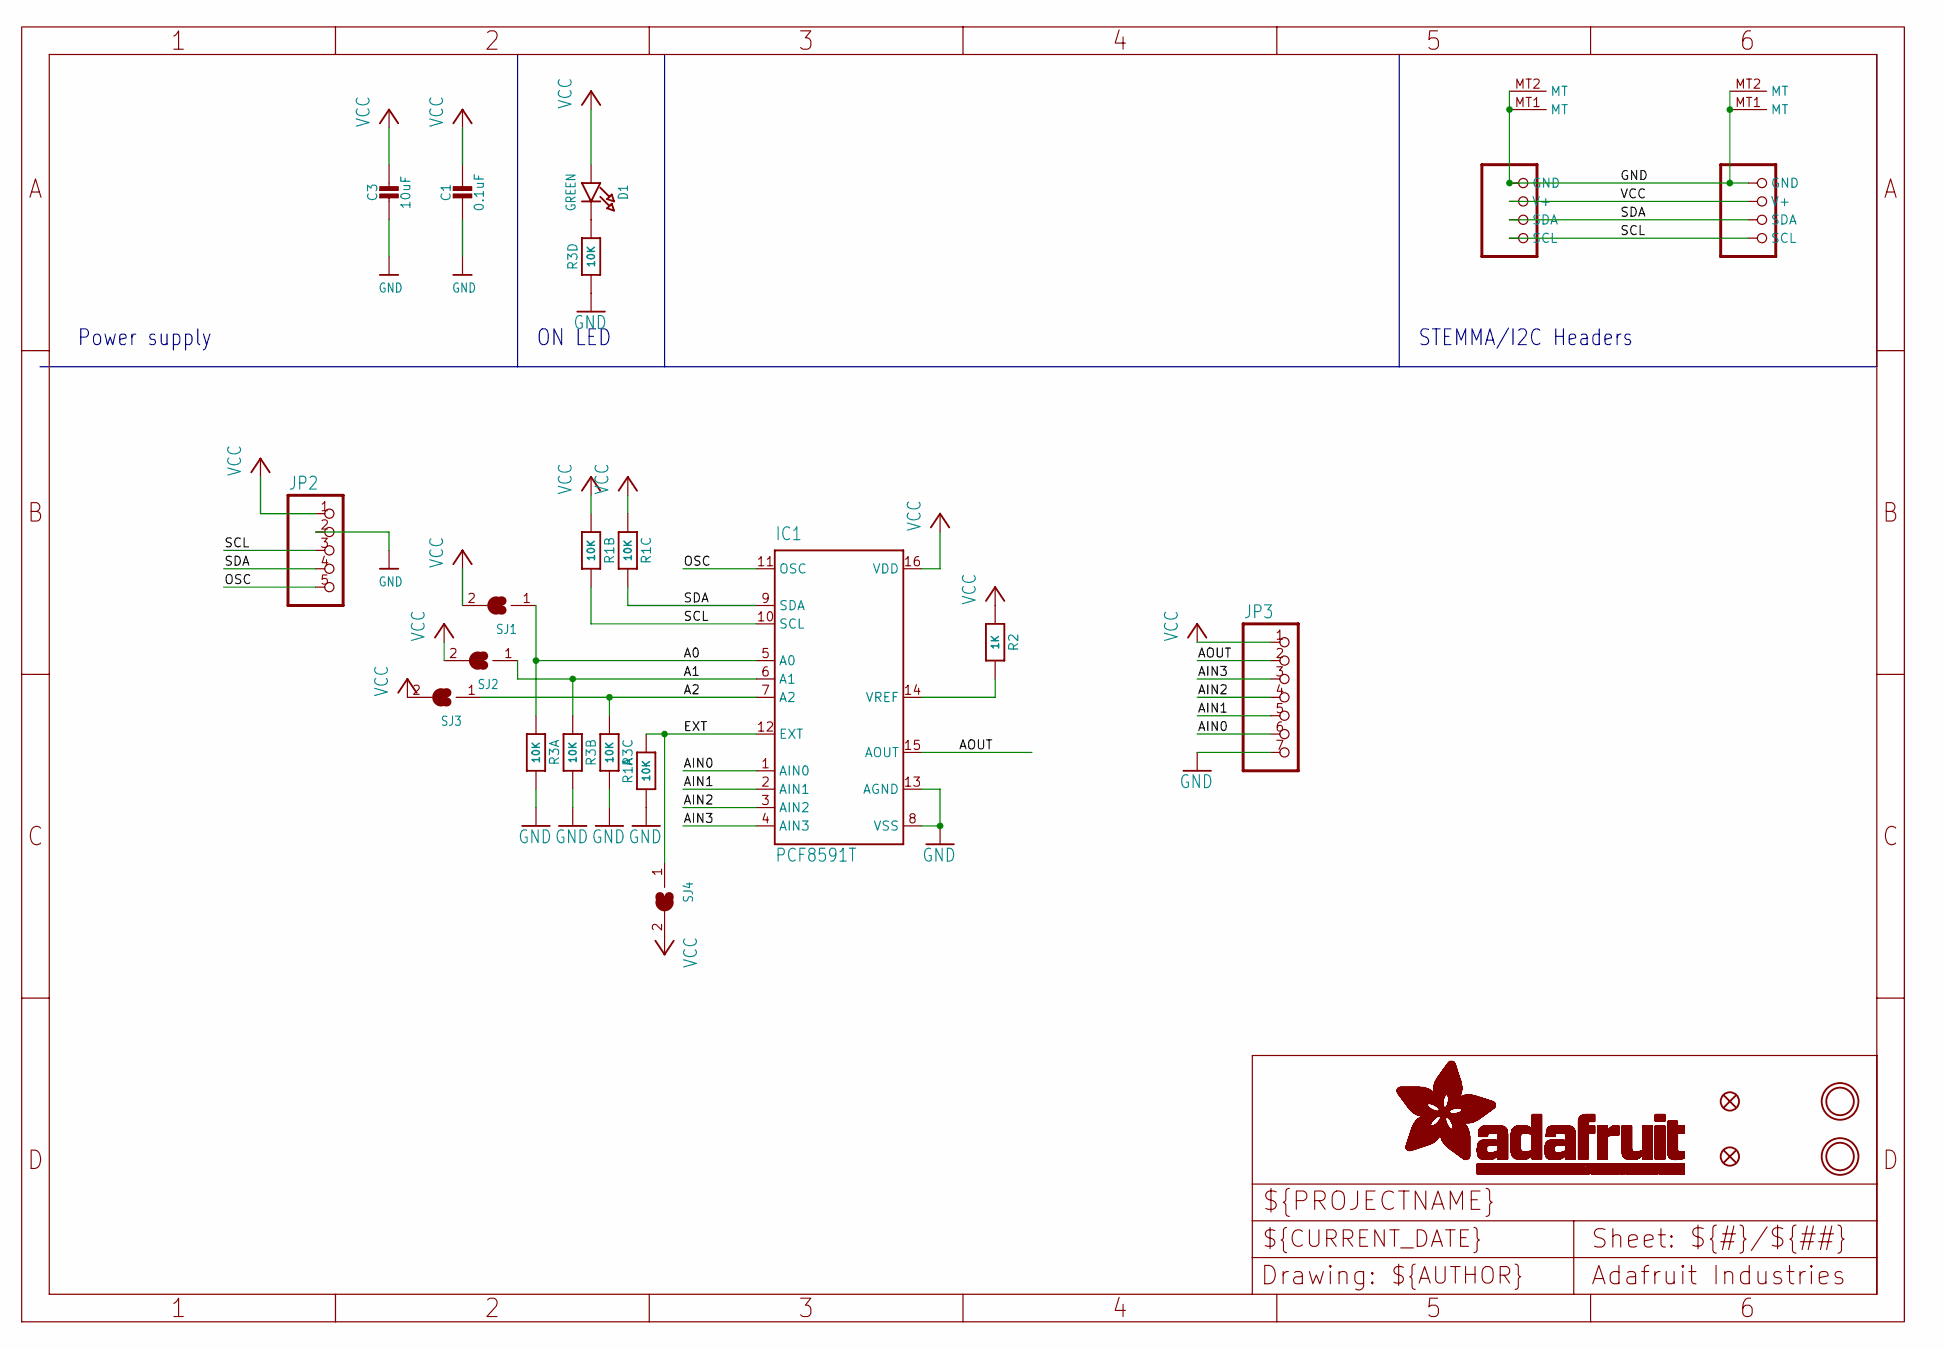
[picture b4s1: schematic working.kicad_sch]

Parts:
C1: 0.1uF; 0603-NO
C3: 10uF; 0805-NO
CONN3, CONN4: STEMMA_I2C_QT; JST_SH4
D1: GREEN; CHIPLED_0603_NOOUTLINE
FID3, FID4: FIDUCIAL_1MM
IC1: PCF8591T; SO16W
JP2: HEADER-1X570MIL; 1X05_ROUND_70
JP3: HEADER-1X770MIL; 1X07_ROUND_70
R1, R3: 10K; RESPACK_4X0603
R2: 1K; 0603-NO
SJ1, SJ2, SJ3, SJ4: SOLDERJUMPER; SOLDERJUMPER_ARROW_NOPASTE
U$19, U$21: MOUNTINGHOLE2.5; MOUNTINGHOLE_2.5_PLATED

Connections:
A0: IC1.5 (A0), R3.1, SJ1.1
A1: IC1.6 (A1), R3.2 (1), SJ2.1
A2: IC1.7 (A2), R3.3 (1), SJ3.1
AIN0: IC1.1 (AIN0), JP3.6
AIN1: IC1.2 (AIN1), JP3.5
AIN2: IC1.3 (AIN2), JP3.4
AIN3: IC1.4 (AIN3), JP3.3
AOUT: IC1.15 (AOUT), JP3.2
EXT: IC1.12 (EXT), R1.8 (2), SJ4.1
GND: C1.2, C3.2, CONN3.1 (GND), CONN3.MT1 (MT), CONN3.MT2 (MT), CONN4.1 (GND), CONN4.MT1 (MT), CONN4.MT2 (MT), IC1.8 (VSS), IC1.13 (AGND), JP2.2, JP3.7, R1.1, R3.4 (1), R3.6 (2), R3.7 (2), R3.8 (2)
unnamed: D1.C, R3.5 (2)
unnamed: IC1.14 (VREF), R2.2
OSC: IC1.11 (OSC), JP2.5
SCL: CONN3.4 (SCL), CONN4.4 (SCL), IC1.10 (SCL), JP2.3, R1.7 (2)
SDA: CONN3.3 (SDA), CONN4.3 (SDA), IC1.9 (SDA), JP2.4, R1.6 (2)
VCC: C1.1, C3.1, CONN3.2 (V+), CONN4.2 (V+), D1.A, IC1.16 (VDD), JP2.1, JP3.1, R1.2 (1), R1.3 (1), R2.1, SJ1.2, SJ2.2, SJ3.2, SJ4.2

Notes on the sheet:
ON LED
Power supply
STEMMA/I2C Headers

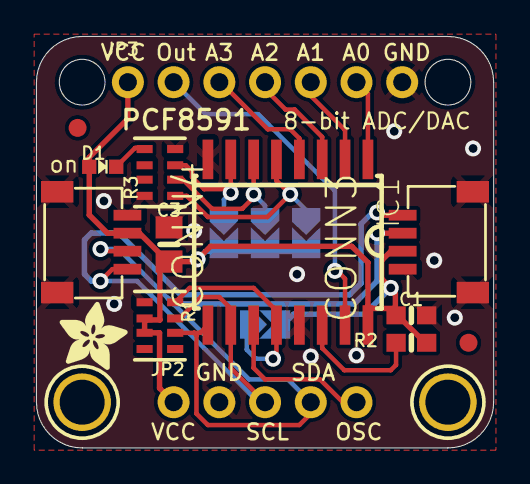
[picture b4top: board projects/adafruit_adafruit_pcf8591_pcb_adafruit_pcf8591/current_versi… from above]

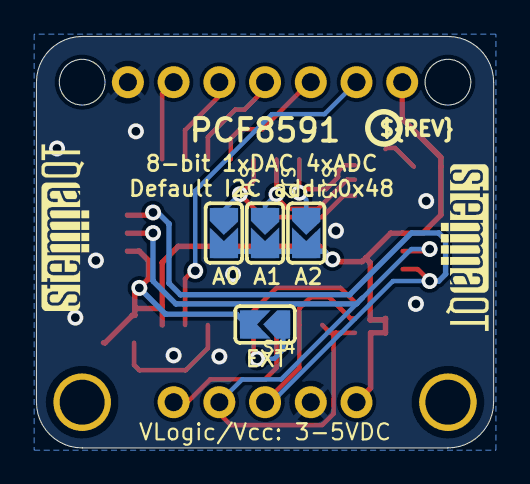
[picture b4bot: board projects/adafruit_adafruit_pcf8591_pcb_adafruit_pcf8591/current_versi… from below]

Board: 2 copper layers, 25.4 x 22.9 mm, 25 parts (7 on the bottom side), 16 nets.

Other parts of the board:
@HOLE0, @HOLE1: (no value)
U$22: ADAFRUIT_3.5MM
U$25: PCBFEAT-REV-040
U$30, U$31: STEMMAQT
